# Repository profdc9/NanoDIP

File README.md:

# Nano-like PCB using ATMEGA328P

Because of the 2021 chip shortage, any chip, especially SMT, is not available.  However, some ATMEGA328Ps can still be had or removed from older devices such as Arduino Uno.

I made a simple PCB that has the Arduino Nano pinout that takes a ATMEGA328P.  It connects to a serial port TTL device, using the DTR line for reset, and can be programmed using the Arduino IDE.  A cheap serial TTL converter is a CP2102 or CP2104 device.

ADC6 and ADC7 are not available because they are not exposed on the ATMEGA328P.

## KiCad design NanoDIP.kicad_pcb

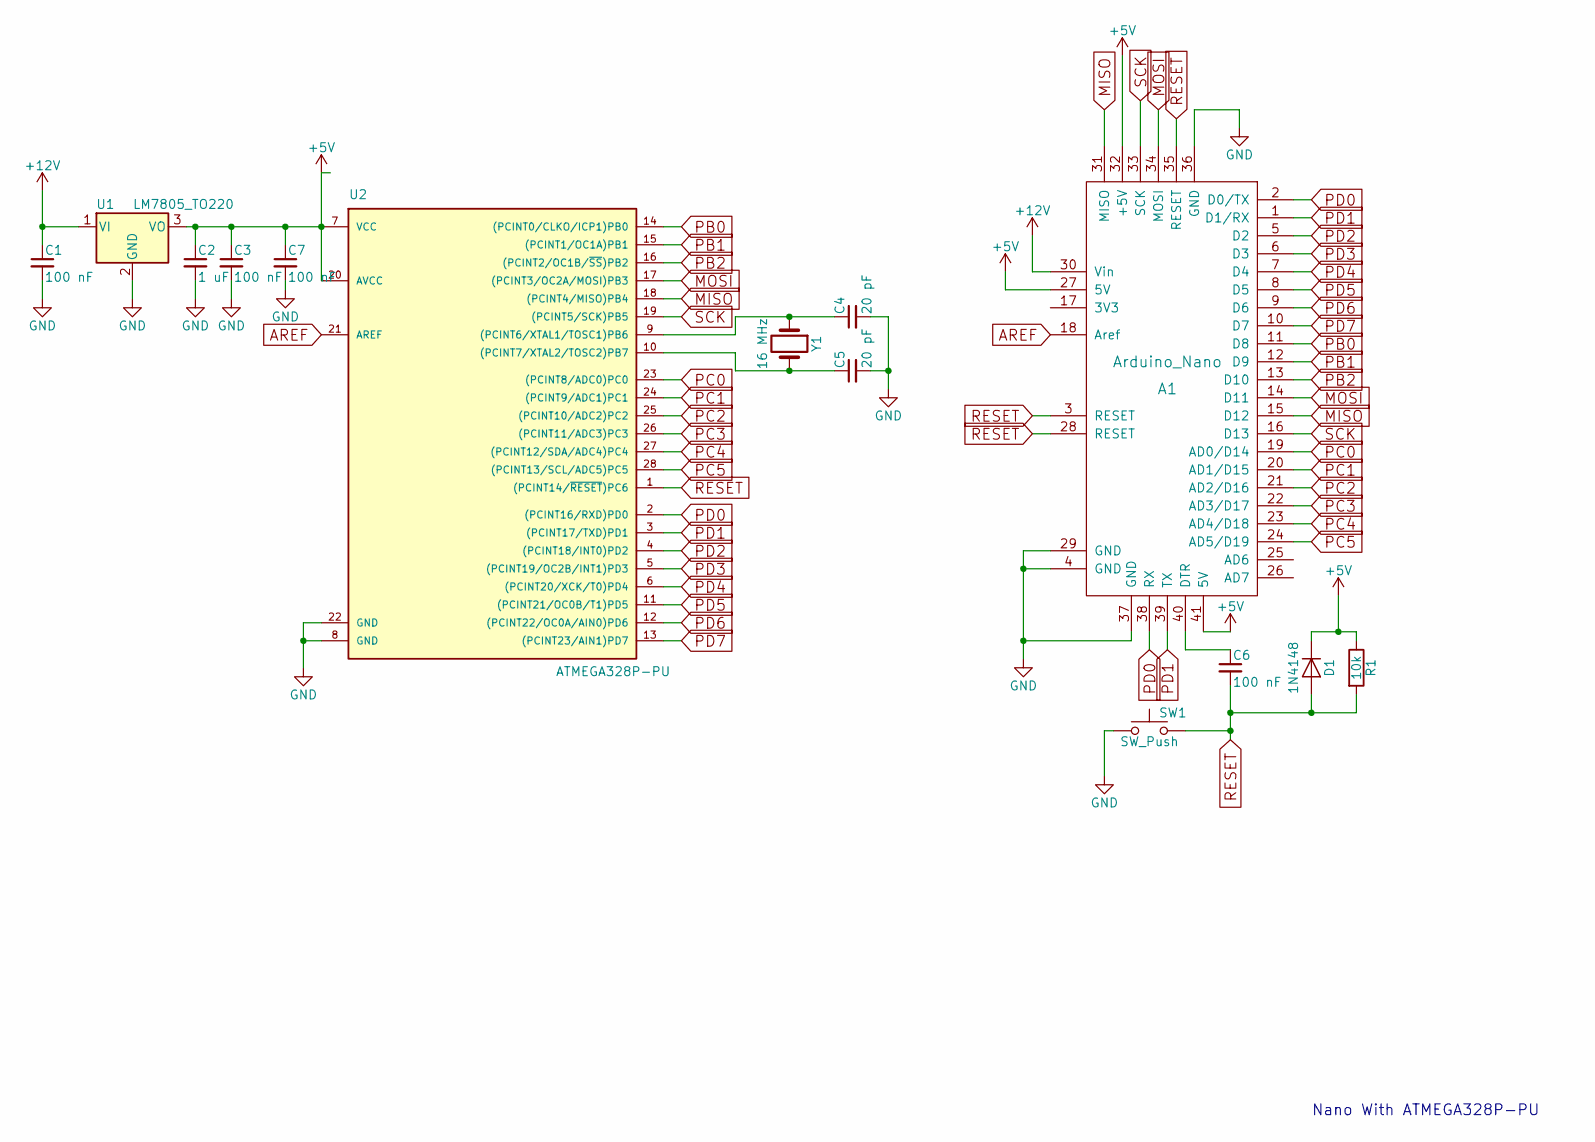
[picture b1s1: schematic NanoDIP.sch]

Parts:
A1: Arduino_Nano
C1, C3, C6, C7: 100 nF; C_Disc_D5.0mm_W2.5mm_P2.50mm
C2: 1 uF; C_Disc_D5.0mm_W2.5mm_P5.00mm
C4, C5: 20 pF; C_Disc_D5.0mm_W2.5mm_P2.50mm
D1: 1N4148; D_DO-35_SOD27_P7.62mm_Horizontal
R1: 10k; R_Axial_DIN0207_L6.3mm_D2.5mm_P7.62mm_Horizontal
SW1: SW_Push; SW_PUSH_6mm
U1: LM7805_TO220; TO-220-3_Vertical
U2: ATMEGA328P-PU; DIP-28_W7.62mm_Socket
Y1: 16 MHz; Crystal_HC49-U_Vertical

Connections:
+5V: A1.27 (5V), A1.32 (+5V), A1.41 (5V), C2.1, C3.1, C7.1, D1.1 (K), R1.1, U1.3 (VO), U2.7 (VCC), U2.20 (AVCC)
+12V: A1.30 (Vin), C1.1, U1.1 (VI)
AREF: A1.18 (Aref), U2.21 (AREF)
GND: A1.4 (GND), A1.29 (GND), A1.36 (GND), A1.37 (GND), C1.2, C2.2, C3.2, C4.2, C5.2, C7.2, SW1.1, U1.2 (GND), U2.8 (GND), U2.22 (GND)
MISO: A1.15 (D12), A1.31 (MISO), U2.18 ((PCINT4/MISO)PB4)
MOSI: A1.14 (D11), A1.34 (MOSI), U2.17 ((PCINT3/OC2A/MOSI)PB3)
unnamed: A1.40 (DTR), C6.1
unnamed: C4.1, U2.9 ((PCINT6/XTAL1/TOSC1)PB6), Y1.1
unnamed: C5.1, U2.10 ((PCINT7/XTAL2/TOSC2)PB7), Y1.2
PB0: A1.11 (D8), U2.14 ((PCINT0/CLKO/ICP1)PB0)
PB1: A1.12 (D9), U2.15 ((PCINT1/OC1A)PB1)
PB2: A1.13 (D10), U2.16 ((PCINT2/OC1B/~SS~)PB2)
PC0: A1.19 (AD0/D14), U2.23 ((PCINT8/ADC0)PC0)
PC1: A1.20 (AD1/D15), U2.24 ((PCINT9/ADC1)PC1)
PC2: A1.21 (AD2/D16), U2.25 ((PCINT10/ADC2)PC2)
PC3: A1.22 (AD3/D17), U2.26 ((PCINT11/ADC3)PC3)
PC4: A1.23 (AD4/D18), U2.27 ((PCINT12/SDA/ADC4)PC4)
PC5: A1.24 (AD5/D19), U2.28 ((PCINT13/SCL/ADC5)PC5)
PD0: A1.2 (D0/TX), A1.38 (RX), U2.2 ((PCINT16/RXD)PD0)
PD1: A1.1 (D1/RX), A1.39 (TX), U2.3 ((PCINT17/TXD)PD1)
PD2: A1.5 (D2), U2.4 ((PCINT18/INT0)PD2)
PD3: A1.6 (D3), U2.5 ((PCINT19/OC2B/INT1)PD3)
PD4: A1.7 (D4), U2.6 ((PCINT20/XCK/T0)PD4)
PD5: A1.8 (D5), U2.11 ((PCINT21/OC0B/T1)PD5)
PD6: A1.9 (D6), U2.12 ((PCINT22/OC0A/AIN0)PD6)
PD7: A1.10 (D7), U2.13 ((PCINT23/AIN1)PD7)
RESET: A1.3 (RESET), A1.28 (RESET), A1.35 (RESET), C6.2, D1.2 (A), R1.2, SW1.2, U2.1 ((PCINT14/~RESET~)PC6)
SCK: A1.16 (D13), A1.33 (SCK), U2.19 ((PCINT5/SCK)PB5)

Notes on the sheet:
Nano With ATMEGA328P-PU

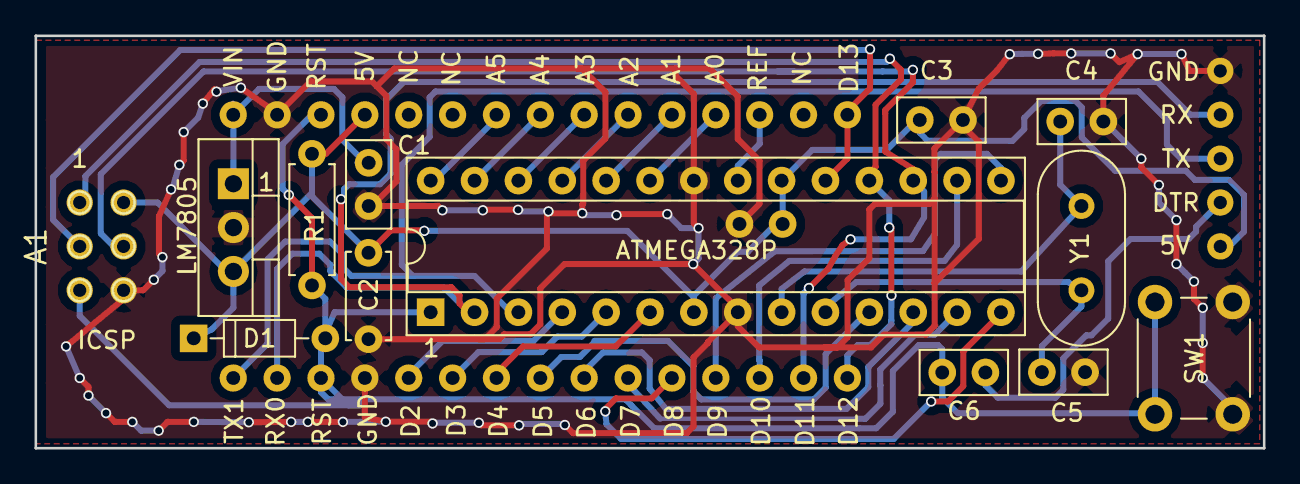
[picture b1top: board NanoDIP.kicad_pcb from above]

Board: 2 copper layers, 71.1 x 23.9 mm, 14 parts (1 on the bottom side), 28 nets.

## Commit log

2021-10-18 Added pin labels
2021-10-18 Added layers, turned around some labels
2021-10-19 Added 5V pin to program header
2021-10-23 JLCPCB order 2021-10-22
2021-11-10 Fixed RX/TX on pins
